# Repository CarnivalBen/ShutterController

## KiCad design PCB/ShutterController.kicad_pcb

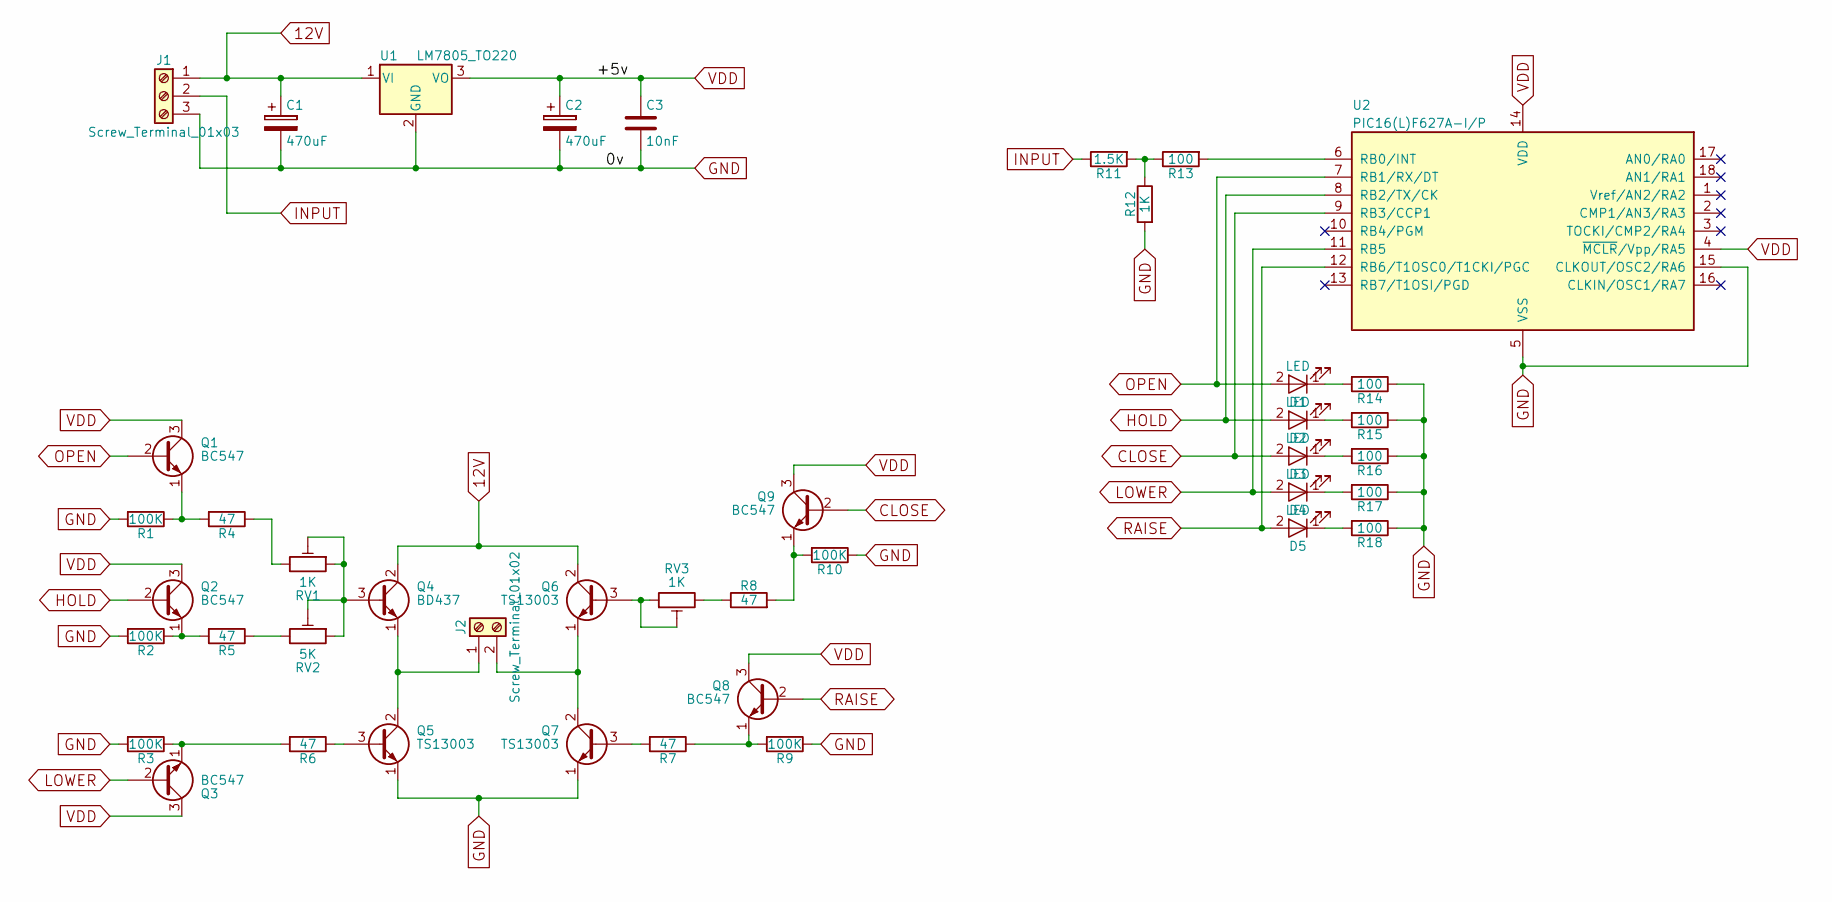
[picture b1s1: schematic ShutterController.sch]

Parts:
C1, C2: 470uF; CP_Radial_D10.0mm_P5.00mm
C3: 10nF; C_Disc_D3.0mm_W1.6mm_P2.50mm
D1, D2, D3, D4, D5: LED; LED_D5.0mm
J1: Screw_Terminal_01x03; TerminalBlock_Phoenix_MKDS1.5-3pol
J2: Screw_Terminal_01x02; TerminalBlock_Phoenix_MKDS1.5-2pol
Q1, Q2, Q3, Q8, Q9: BC547; TO-92_Inline_Wide
Q4: BD437; TO-220-3_Vertical
Q5, Q6, Q7: TS13003; TO-92_Inline_Wide
R1, R2, R3, R9, R10: 100K; R_Axial_DIN0207_L6.3mm_D2.5mm_P10.16mm_Horizontal
R4, R5, R6, R7, R8: 47; R_Axial_DIN0207_L6.3mm_D2.5mm_P10.16mm_Horizontal
R11: 1.5K; R_Axial_DIN0207_L6.3mm_D2.5mm_P10.16mm_Horizontal
R12: 1K; R_Axial_DIN0207_L6.3mm_D2.5mm_P10.16mm_Horizontal
R13, R14, R15, R16, R17, R18: 100; R_Axial_DIN0207_L6.3mm_D2.5mm_P10.16mm_Horizontal
RV1, RV3: 1K; Potentiometer_Trimmer_Piher_PT-10v5_Horizontal_Px5.0mm_Py5.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
RV2: 5K; Potentiometer_Trimmer_Piher_PT-10v5_Horizontal_Px5.0mm_Py5.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
U1: LM7805_TO220; TO-220-3_Vertical
U2: PIC16(L)F627A-I/P; DIP-18_W7.62mm_LongPads

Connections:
12V: C1.1, J1.1, Q4.2 (C), Q6.2 (C), U1.1 (VI)
CLOSE: D3.2 (A), Q9.2 (B), U2.9 (RB3/CCP1)
GND: C1.2, C2.2, C3.2, J1.3, Q5.1 (E), Q7.1 (E), R1.2, R2.2, R3.2, R9.1, R10.1, R12.2, R14.1, R15.1, R16.1, R17.1, R18.1, U1.2 (GND), U2.5 (VSS), U2.15 (CLKOUT/OSC2/RA6)
HOLD: D2.2 (A), Q2.2 (B), U2.8 (RB2/TX/CK)
INPUT: J1.2, R11.1
LOWER: D4.2 (A), Q3.2 (B), U2.11 (RB5)
unnamed: D1.1 (K), R14.2
unnamed: D2.1 (K), R15.2
unnamed: D3.1 (K), R16.2
unnamed: D4.1 (K), R17.2
unnamed: D5.1 (K), R18.2
unnamed: J2.1, Q4.1 (E), Q5.2 (C)
unnamed: J2.2, Q6.1 (E), Q7.2 (C)
unnamed: Q1.1 (E), R1.1, R4.2
unnamed: Q2.1 (E), R2.1, R5.2
unnamed: Q3.1 (E), R3.1, R6.2
unnamed: Q4.3 (B), RV1.1, RV1.2, RV2.1, RV2.2
unnamed: Q5.3 (B), R6.1
unnamed: Q6.3 (B), RV3.1, RV3.2
unnamed: Q7.3 (B), R7.2
unnamed: Q8.1 (E), R7.1, R9.2
unnamed: Q9.1 (E), R8.2, R10.2
unnamed: R4.1, RV1.3
unnamed: R5.1, RV2.3
unnamed: R8.1, RV3.3
unnamed: R11.2, R12.1, R13.1
unnamed: R13.2, U2.6 (RB0/INT)
OPEN: D1.2 (A), Q1.2 (B), U2.7 (RB1/RX/DT)
RAISE: D5.2 (A), Q8.2 (B), U2.12 (RB6/T1OSC0/T1CKI/PGC)
VDD: C2.1, C3.1, Q1.3 (C), Q2.3 (C), Q3.3 (C), Q8.3 (C), Q9.3 (C), U1.3 (VO), U2.4 (~MCLR~/Vpp/RA5), U2.14 (VDD)

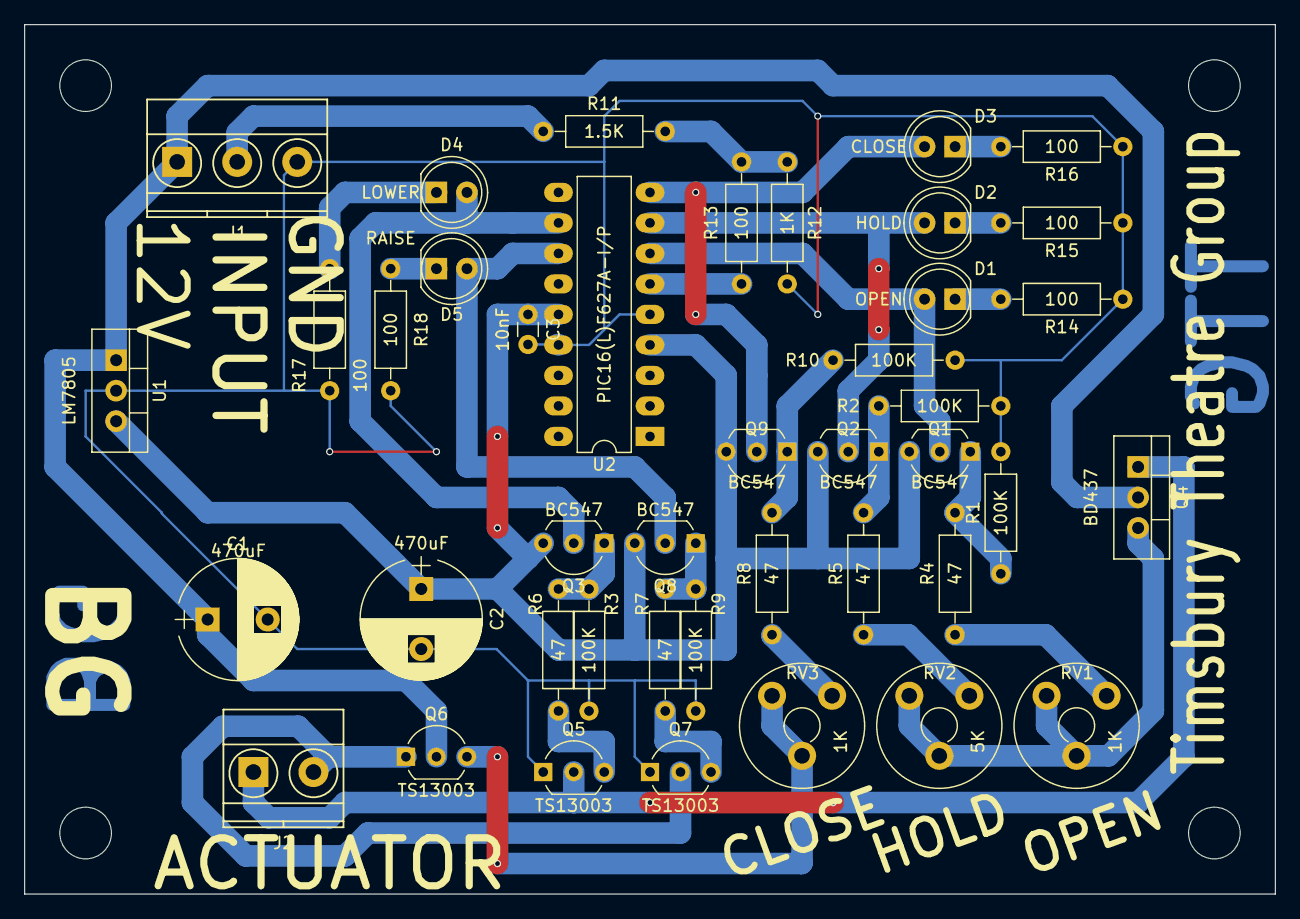
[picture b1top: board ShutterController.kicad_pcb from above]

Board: 2 copper layers, 104.1 x 72.4 mm, 42 parts (0 on the bottom side), 30 nets.

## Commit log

2018-04-01 Added main source first draft.
2018-04-06 First version complete
